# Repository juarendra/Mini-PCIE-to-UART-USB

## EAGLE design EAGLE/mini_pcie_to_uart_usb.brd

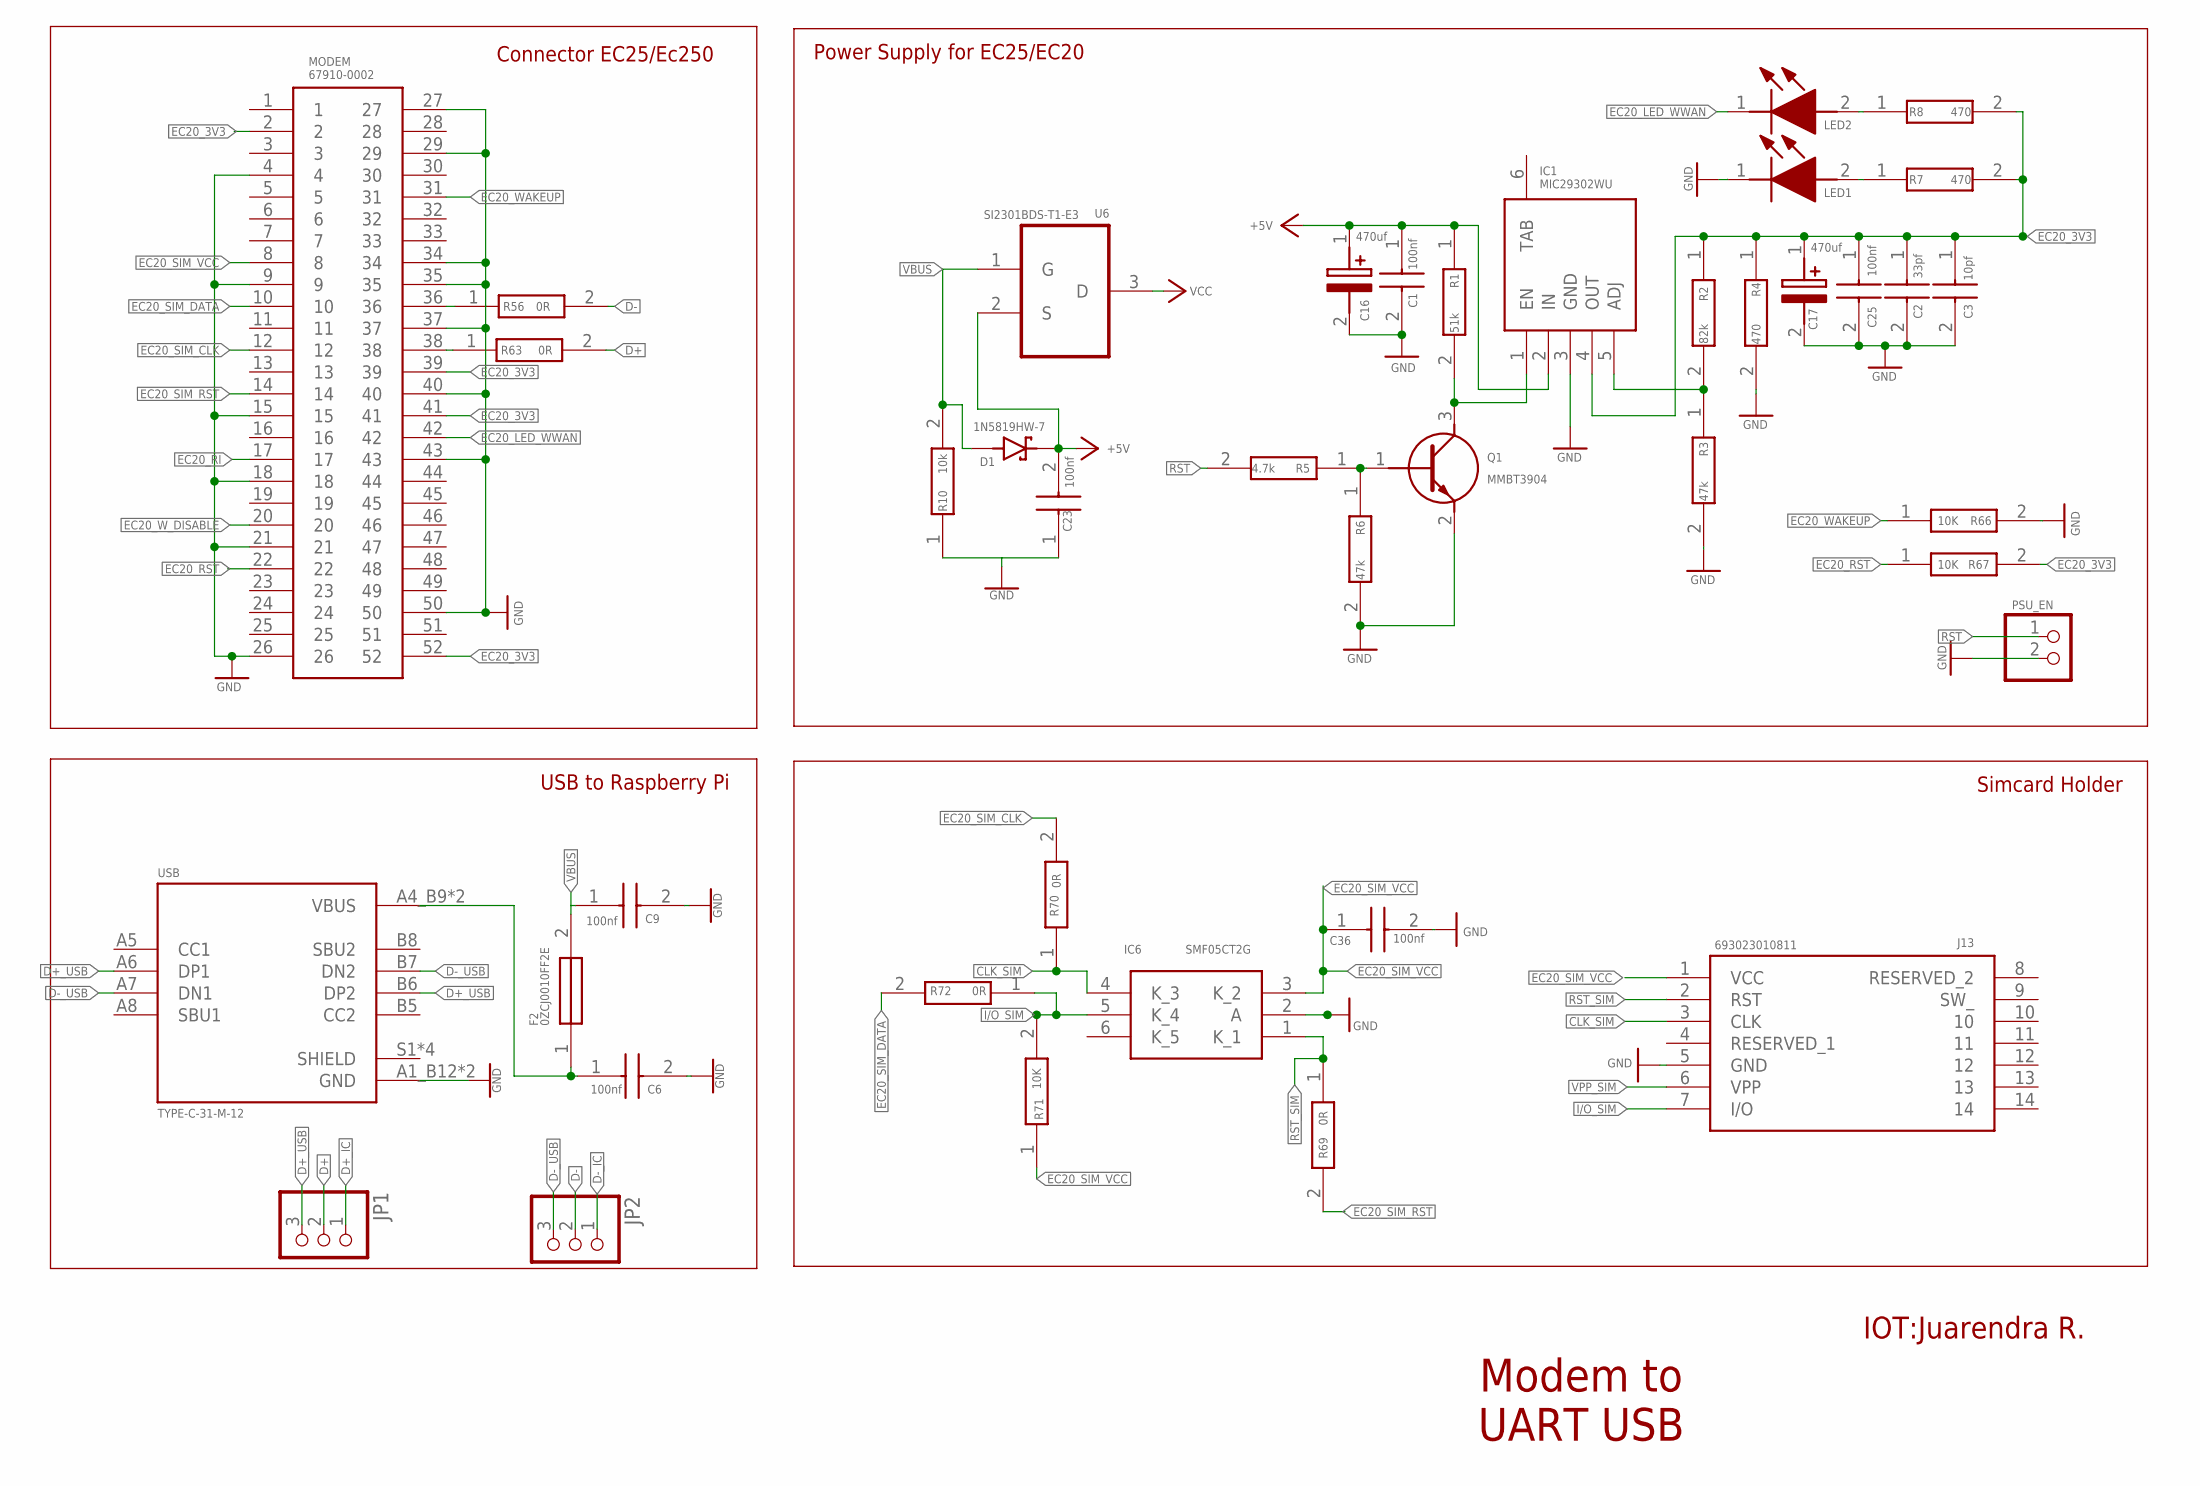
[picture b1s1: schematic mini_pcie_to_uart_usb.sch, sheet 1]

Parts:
C1, C25, C36: 100nf; CAPC1608X90N
C2: 33pf; CAPC1608X90N
C3: 10pf; CAPC1608X90N
C6, C9, C23: 100nf; CAPC1608X87N
C16, C17: 470uf; CAPPM7343X310N
D1: 1N5819HW-7; SOD3715X145N
F2: 0ZCJ0010FF2E; FUSC3216X75N
IC1: MIC29302WU
IC6: SMF05CT2G; SOT65P210X110-6N
J13: 693023010811
JP1, JP2: PINHD-1X3; 1X03
LED1, LED2: HSMR-C170-R0000; LEDC2012X90N
MODEM: 67910-0002; 67910-5700
PSU_EN: PINHD-1X2; 1X02
Q1: MMBT3904; SOT95P240X120-3N
R1: 51k; ERJP03_PA3_(0603)
R2: 82k; RESC1609X55N
R3, R6: 47k; RESC1609X55N
R4, R7, R8: 470; RESC1609X55N
R5: 4.7k; RESC1609X55N
R10: 10k; RESC1608X55N
R56, R63, R69, R70, R72: 0R; RESC1608X55N
R66, R67, R71: 10K; RESC1608X55N
U6: SI2301BDS-T1-E3; SOT95P237X112-3N
USB: TYPE-C-31-M-12; HRO_TYPE-C-31-M-12

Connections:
+5V: C1.1, C16.1 (+), C23.2, D1.C (K), IC1.2 (IN), R1.1, U6.2 (S)
CLK_SIM: IC6.4 (K_3), J13.3 (CLK), R70.1
D+: JP1.2, R63.2
D+_IC: JP1.1; also elsewhere on the board
D+_USB: JP1.3, USB.A6 (DP1), USB.B6 (DP2)
D-: JP2.2, R56.2
D-_IC: JP2.1; also elsewhere on the board
D-_USB: JP2.3, USB.A7 (DN1), USB.B7 (DN2)
EC20_3V3: C2.1, C3.1, C17.1 (+), C25.1, IC1.4 (OUT), MODEM.2, MODEM.39, MODEM.41, MODEM.52, R2.1, R4.1, R7.2, R8.2, R67.2; also elsewhere on the board
EC20_LED_WWAN: LED2.1 (K), MODEM.42
EC20_RI: MODEM.17
EC20_RST: MODEM.22, R67.1; also elsewhere on the board
EC20_SIM_CLK: MODEM.12, R70.2
EC20_SIM_DATA: MODEM.10, R72.2
EC20_SIM_RST: MODEM.14, R69.2
EC20_SIM_VCC: C36.1, IC6.3 (K_2), J13.1 (VCC), MODEM.8, R71.1
EC20_WAKEUP: MODEM.31, R66.1; also elsewhere on the board
EC20_W_DISABLE: MODEM.20
GND: C1.2, C2.2, C3.2, C6.2, C9.2, C16.2 (-), C17.2 (-), C23.1, C25.2, C36.2, IC1.3 (GND), IC6.2 (A), J13.5 (GND), LED1.1 (K), MODEM.4, MODEM.9, MODEM.15, MODEM.18, MODEM.21, MODEM.26, MODEM.27, MODEM.29, MODEM.34, MODEM.35, MODEM.37, MODEM.40, MODEM.43, MODEM.50, PSU_EN.2, Q1.2 (E), R3.2, R4.2, R6.2, R10.1, R66.2, USB.A1_B12 (GND), USB.B1_A12 (GND); also elsewhere on the board
I/O_SIM: IC6.5 (K_4), J13.7 (I/O), R71.2, R72.1
unnamed: IC1.1 (EN), Q1.3 (C), R1.2
unnamed: IC1.5 (ADJ), R2.2, R3.1
unnamed: Q1.1 (B), R5.1, R6.1
unnamed: LED1.2 (A), R7.1
unnamed: C6.1, F2.1, USB.A4_B9 (VBUS), USB.B4_A9 (VBUS)
unnamed: LED2.2 (A), R8.1
unnamed: MODEM.38, R63.1
unnamed: MODEM.36, R56.1
RST: PSU_EN.1, R5.2
RST_SIM: IC6.1 (K_1), J13.2 (RST), R69.1
VBUS: C9.1, D1.A, F2.2, R10.2, U6.1 (G); also elsewhere on the board
VCC: U6.3 (D); also elsewhere on the board
VPP_SIM: J13.6 (VPP)

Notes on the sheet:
Modem to UART USB
IOT:Juarendra R.
USB to Raspberry Pi
Simcard Holder
Power Supply for EC25/EC20
Connector EC25/Ec250

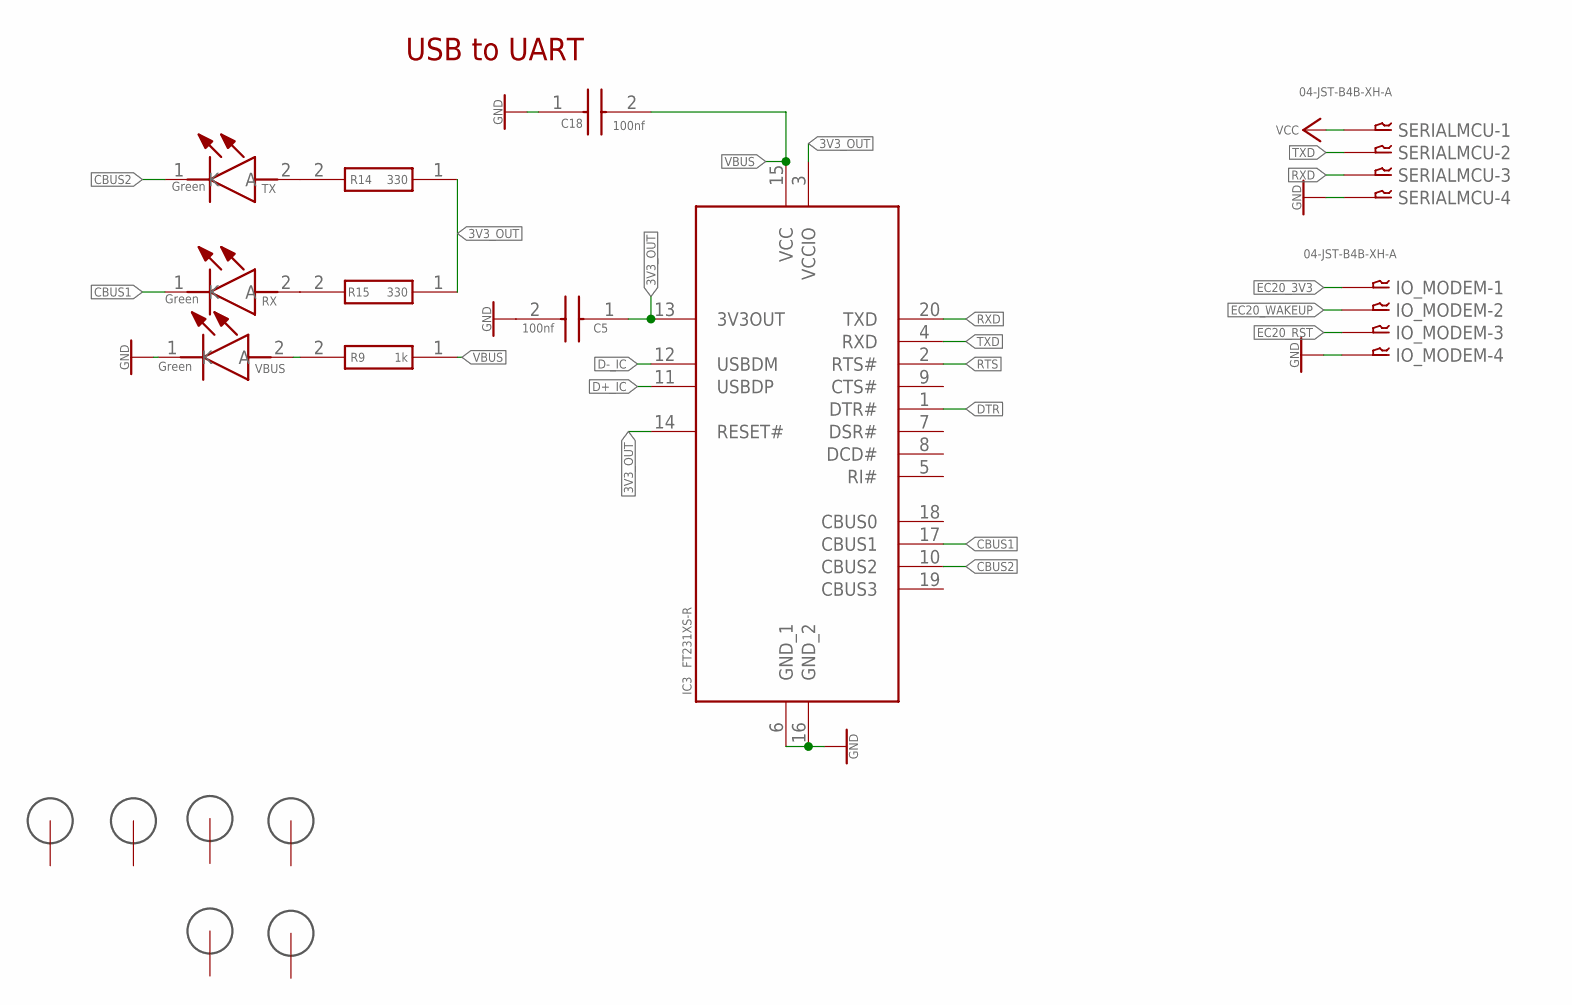
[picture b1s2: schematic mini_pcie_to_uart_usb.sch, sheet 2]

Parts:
C5, C18: 100nf; CAPC1608X87N
H1, H2, H3, H4, H5, H6: 3MM_HOLE
IC3: FT231XS-R; SOP64P599X175-20N
IO_MODEM: 04-JST-B4B-XH-A; B4B-XH
R9: 1k; RESC1608X55N
R14, R15: 330; ERJH3
RX: Green; LEDC2012X80N
SERIALMCU: 04-JST-B4B-XH-A; B4B-XH
TX: Green; LEDC2012X80N
VBUS: Green; LEDC2012X80N

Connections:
3V3_OUT: C5.1, IC3.3 (VCCIO), IC3.13 (3V3OUT), IC3.14 (RESET#), R14.1, R15.1
CBUS1: IC3.17 (CBUS1), RX.1 (K)
CBUS2: IC3.10 (CBUS2), TX.1 (K)
D+_IC: IC3.11 (USBDP); also elsewhere on the board
D-_IC: IC3.12 (USBDM); also elsewhere on the board
DTR: IC3.1 (DTR#)
EC20_3V3: IO_MODEM.P$1; also elsewhere on the board
EC20_RST: IO_MODEM.P$3; also elsewhere on the board
EC20_WAKEUP: IO_MODEM.P$2; also elsewhere on the board
GND: C5.2, C18.1, IC3.6 (GND_1), IC3.16 (GND_2), IO_MODEM.P$4, SERIALMCU.P$4, VBUS.1 (K); also elsewhere on the board
unnamed: R15.2, RX.2 (A)
unnamed: R9.2, VBUS.2 (A)
unnamed: R14.2, TX.2 (A)
RTS: IC3.2 (RTS#)
RXD: IC3.20 (TXD), SERIALMCU.P$3
TXD: IC3.4 (RXD), SERIALMCU.P$2
VBUS: C18.2, IC3.15 (VCC), R9.1; also elsewhere on the board
VCC: SERIALMCU.P$1; also elsewhere on the board

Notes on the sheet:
USB to UART

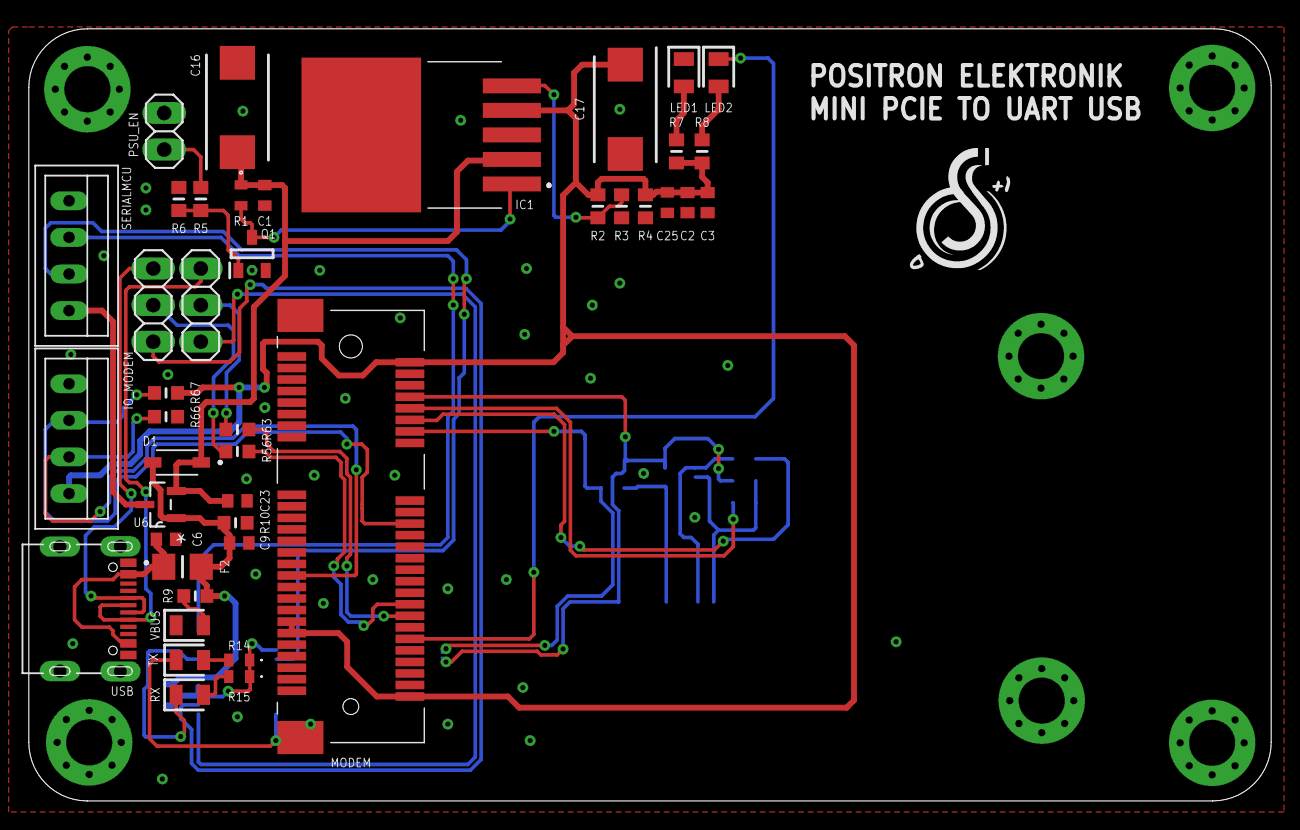
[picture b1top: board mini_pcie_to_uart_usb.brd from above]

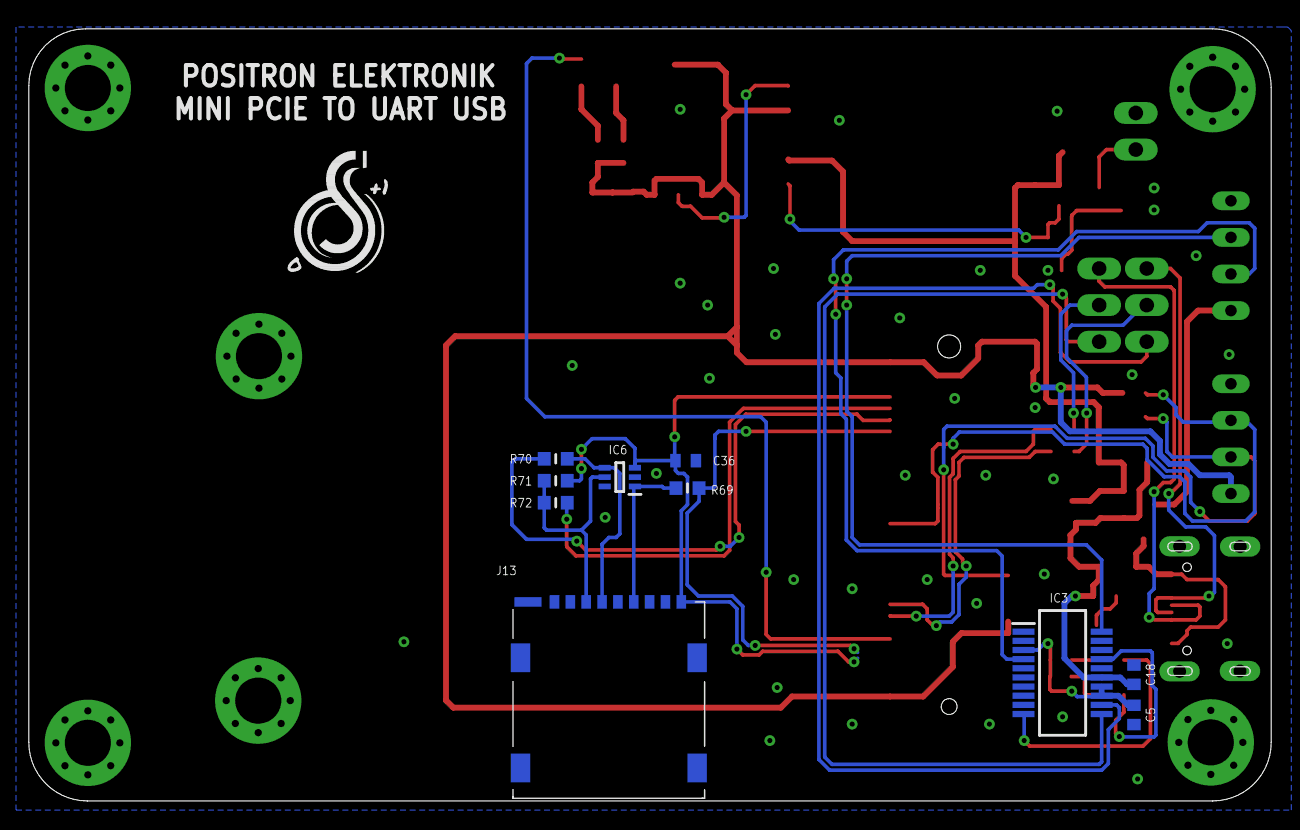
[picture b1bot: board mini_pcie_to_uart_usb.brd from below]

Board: 2 copper layers, 86.2 x 53.6 mm, 58 parts (10 on the bottom side), 38 nets.

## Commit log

2024-11-29 FEAT: add psu switchover
2024-11-30 FEAT: add connector to mcu
2024-11-30 FEAT: update layout pcb
2024-11-30 FEAT: update route pcb
2024-12-04 FEAT: update 3d pcb
2024-12-04 FEAT: update pcb and file documentation
2024-12-04 DOC: update documentation link dimension file
2024-12-04 FEAT: add schematic
2024-12-04 FEAT: update
2024-12-04 DOC: update documentation link schematic
2024-12-04 FEAT: add pinout
2024-12-04 DOC: update documentation link pinout
